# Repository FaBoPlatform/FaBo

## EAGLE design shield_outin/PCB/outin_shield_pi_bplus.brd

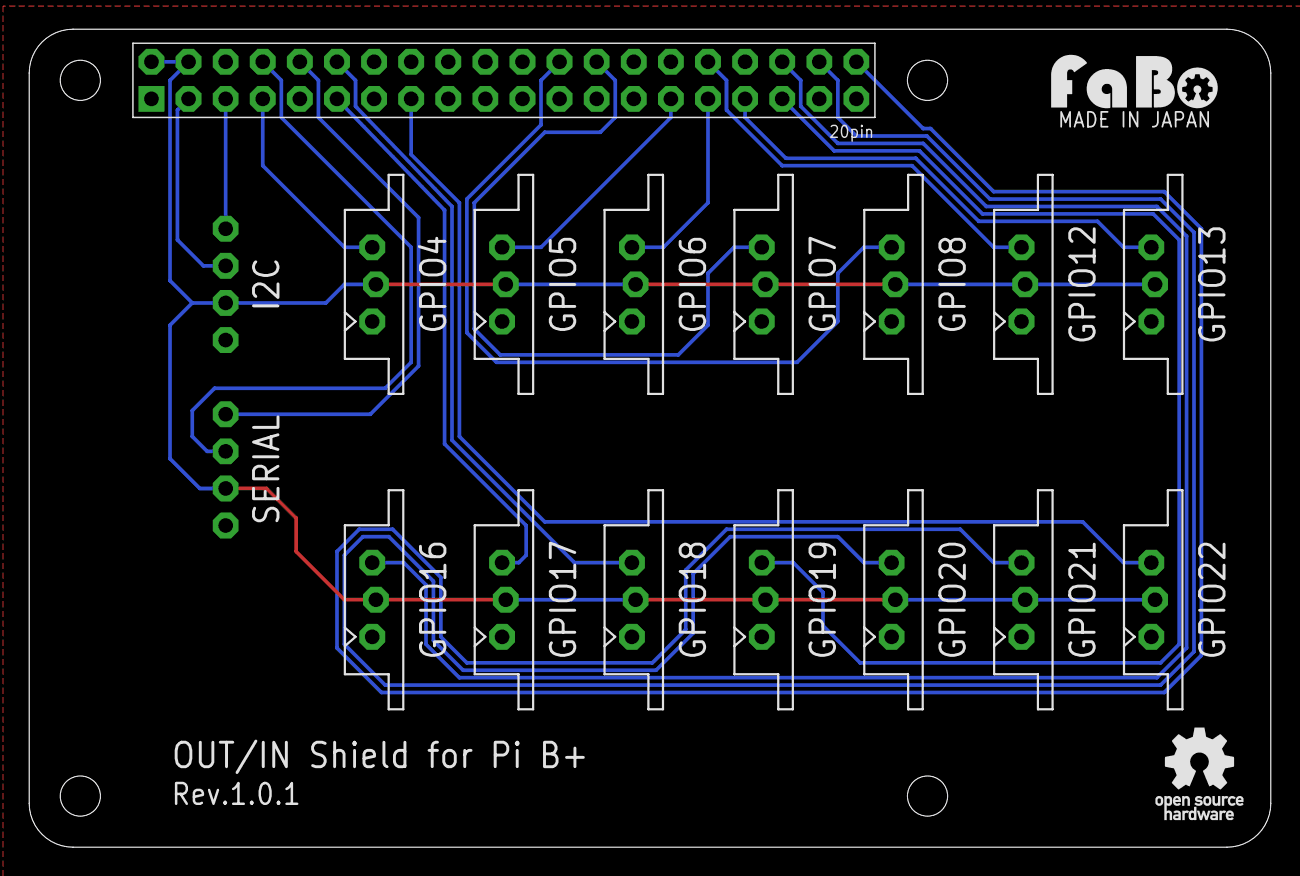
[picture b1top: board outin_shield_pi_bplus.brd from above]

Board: 2 copper layers, 85.0 x 56.0 mm, 19 parts (0 on the bottom side), 20 nets.

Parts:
GPIO4, GPIO5, GPIO6, GPIO7, GPIO8, GPIO12, GPIO13, GPIO16, GPIO17, GPIO18, GPIO19, GPIO20, GPIO21, GPIO22: FABO_BRICK_3PIN_HEADER
I2C: FABO_BRICK_I2C_CONNECTOR
SERIAL: FABO_BRICK_SERIAL_CONNECTOR
U1: RASPBERRY_PI_B+
U$4: LOGO_OSHW_T_M
U$14: LOGO_FABO_M

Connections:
5V: GPIO4.VCC, GPIO5.VCC, GPIO6.VCC, GPIO7.VCC, GPIO8.VCC, GPIO12.VCC, GPIO13.VCC, GPIO16.VCC, GPIO17.VCC, GPIO18.VCC, GPIO19.VCC, GPIO20.VCC, GPIO21.VCC, GPIO22.VCC, I2C.VCC, SERIAL.VCC, U1.2, U1.4
GND: GPIO4.GND, GPIO5.GND, GPIO6.GND, GPIO7.GND, GPIO8.GND, GPIO12.GND, GPIO13.GND, GPIO16.GND, GPIO17.GND, GPIO18.GND, GPIO19.GND, GPIO20.GND, GPIO21.GND, GPIO22.GND, I2C.GND, SERIAL.GND, U1.6, U1.9, U1.14, U1.20, U1.25, U1.30, U1.34, U1.39
GPIO4: GPIO4.I/O, U1.7
GPIO5: GPIO5.I/O, U1.29
GPIO6: GPIO6.I/O, U1.31
GPIO7: GPIO7.I/O, U1.26
GPIO8: GPIO8.I/O, U1.24
GPIO12: GPIO12.I/O, U1.32
GPIO13: GPIO13.I/O, U1.33
GPIO16: GPIO16.I/O, U1.36
GPIO17: GPIO17.I/O, U1.11
GPIO18: GPIO18.I/O, U1.12
GPIO19: GPIO19.I/O, U1.35
GPIO20: GPIO20.I/O, U1.38
GPIO21: GPIO21.I/O, U1.40
GPIO22: GPIO22.I/O, U1.15
RX: SERIAL.RX, U1.10
SCL: I2C.SCL, U1.5
SDA: I2C.SDA, U1.3
TX: SERIAL.TX, U1.8

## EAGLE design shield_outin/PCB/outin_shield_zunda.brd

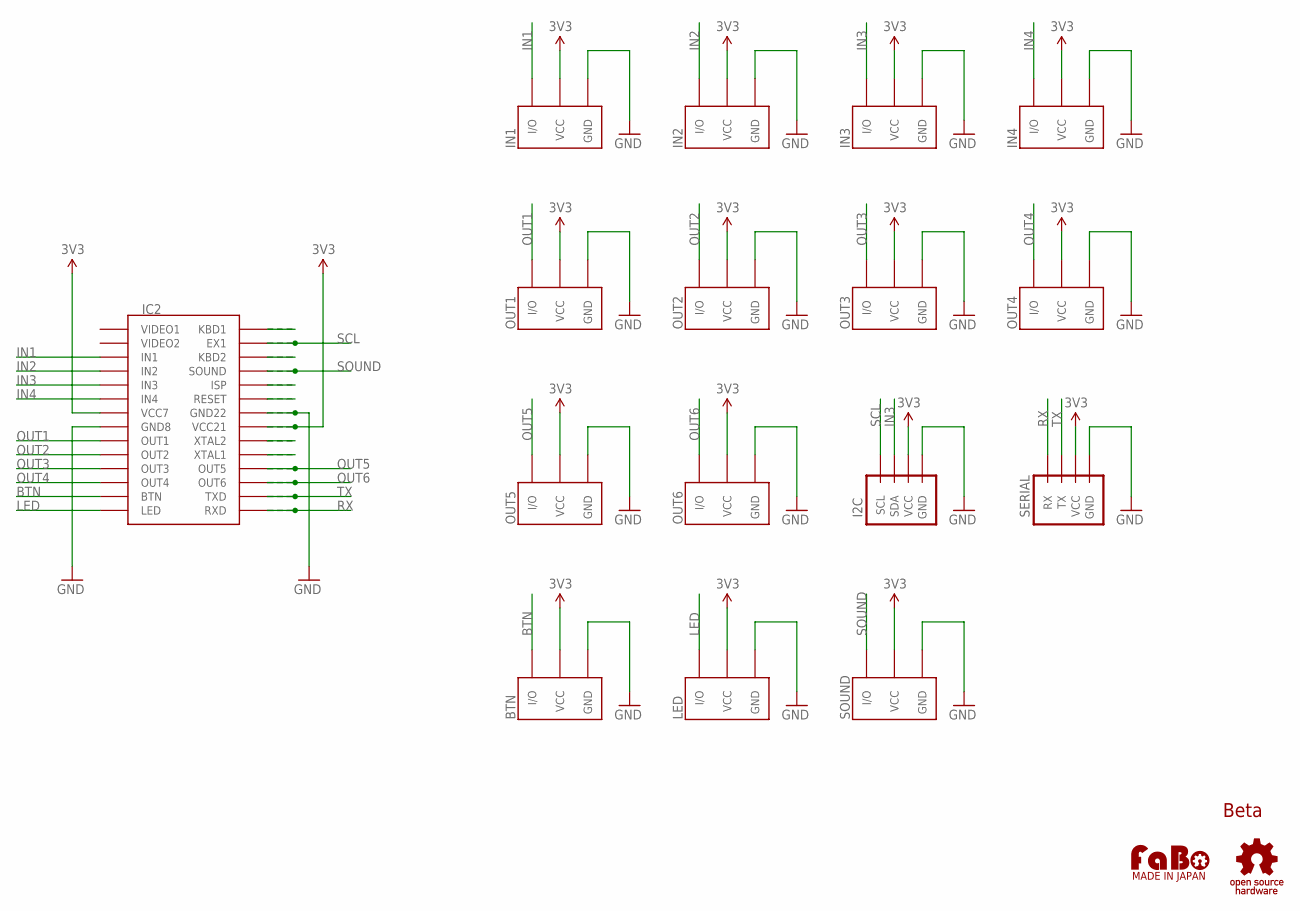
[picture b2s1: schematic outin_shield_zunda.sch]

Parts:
BTN: BRICK_3PIN_CONNECTOR
I2C: BRICK_I2C_CONNECTOR
IN1, IN2, IN3, IN4: BRICK_3PIN_CONNECTOR
LED: BRICK_3PIN_CONNECTOR
OUT1, OUT2, OUT3, OUT4, OUT5, OUT6: BRICK_3PIN_CONNECTOR
SERIAL: BRICK_SERIAL_CONNECTOR
SOUND: BRICK_3PIN_CONNECTOR
U$1: ICHIGOJAM-HOLE; ICHIGOJAM_HOLE
U$3: LOGO_FABO-M; LOGO_FABO_M
U$4: LOGO_OSHW_T-M; LOGO_OSHW_T_M

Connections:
3V3: BTN.VCC, I2C.VCC, IN1.VCC, IN2.VCC, IN3.VCC, IN4.VCC, LED.VCC, OUT1.VCC, OUT2.VCC, OUT3.VCC, OUT4.VCC, OUT5.VCC, OUT6.VCC, SERIAL.VCC, SOUND.VCC, U$1.VCC7, U$1.VCC21, U$1.VCC21-2
BTN: BTN.IN/OUT (I/O), U$1.BTN
GND: BTN.GND, I2C.GND, IN1.GND, IN2.GND, IN3.GND, IN4.GND, LED.GND, OUT1.GND, OUT2.GND, OUT3.GND, OUT4.GND, OUT5.GND, OUT6.GND, SERIAL.GND, SOUND.GND, U$1.GND8, U$1.GND22, U$1.GND22-2
IN1: IN1.IN/OUT (I/O), U$1.IN1
IN2: IN2.IN/OUT (I/O), U$1.IN2
IN3: I2C.SDA, IN3.IN/OUT (I/O), U$1.IN3
IN4: IN4.IN/OUT (I/O), U$1.IN4
LED: LED.IN/OUT (I/O), U$1.LED
unnamed: U$1.KBD1, U$1.KBD1-2
unnamed: U$1.KBD2, U$1.KBD2-2
unnamed: U$1.ISP, U$1.ISP-2
unnamed: U$1.RESET, U$1.RESET-2
unnamed: U$1.XTAL2, U$1.XTAL2-2
unnamed: U$1.XTAL1, U$1.XTAL1-2
OUT1: OUT1.IN/OUT (I/O), U$1.OUT1
OUT2: OUT2.IN/OUT (I/O), U$1.OUT2
OUT3: OUT3.IN/OUT (I/O), U$1.OUT3
OUT4: OUT4.IN/OUT (I/O), U$1.OUT4
OUT5: OUT5.IN/OUT (I/O), U$1.OUT5, U$1.OUT5-2
OUT6: OUT6.IN/OUT (I/O), U$1.OUT6, U$1.OUT6-2
RX: SERIAL.RX, U$1.RXD, U$1.RXD-2
SCL: I2C.SCL, U$1.EX1, U$1.EX1-2
SOUND: SOUND.IN/OUT (I/O), U$1.SOUND, U$1.SOUND-2
TX: SERIAL.TX, U$1.TXD, U$1.TXD-2

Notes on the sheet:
Beta
MADE IN JAPAN

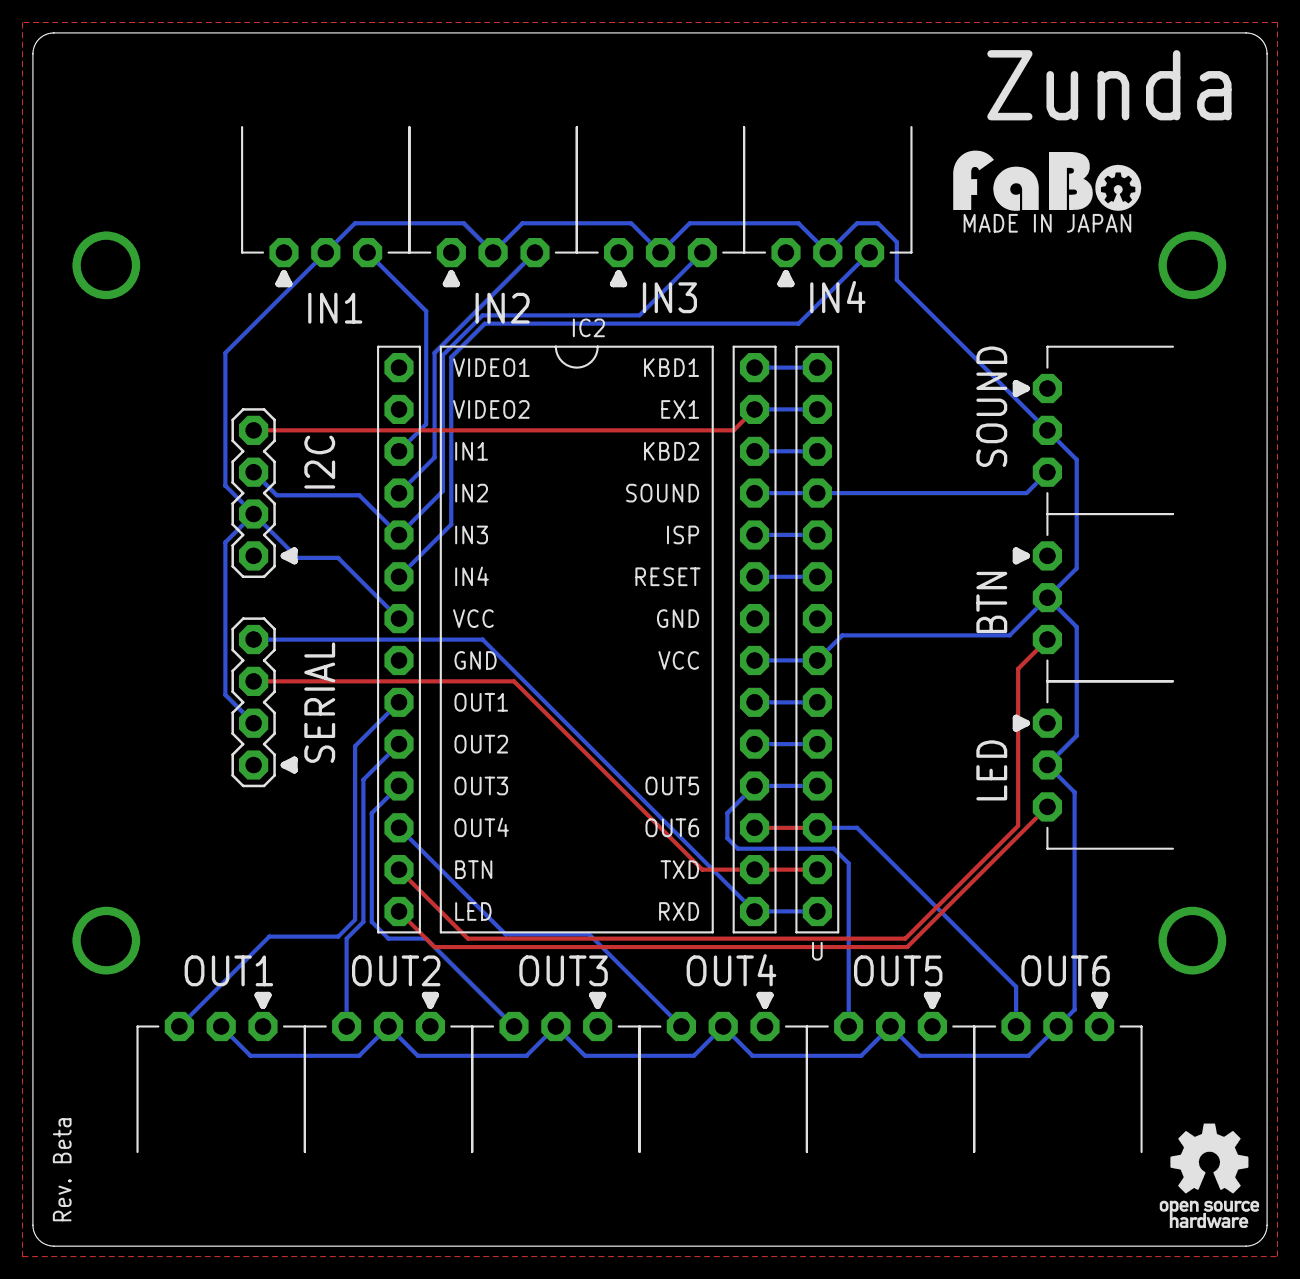
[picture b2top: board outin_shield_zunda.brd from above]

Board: 2 copper layers, 74.9 x 73.7 mm, 18 parts (0 on the bottom side), 24 nets.

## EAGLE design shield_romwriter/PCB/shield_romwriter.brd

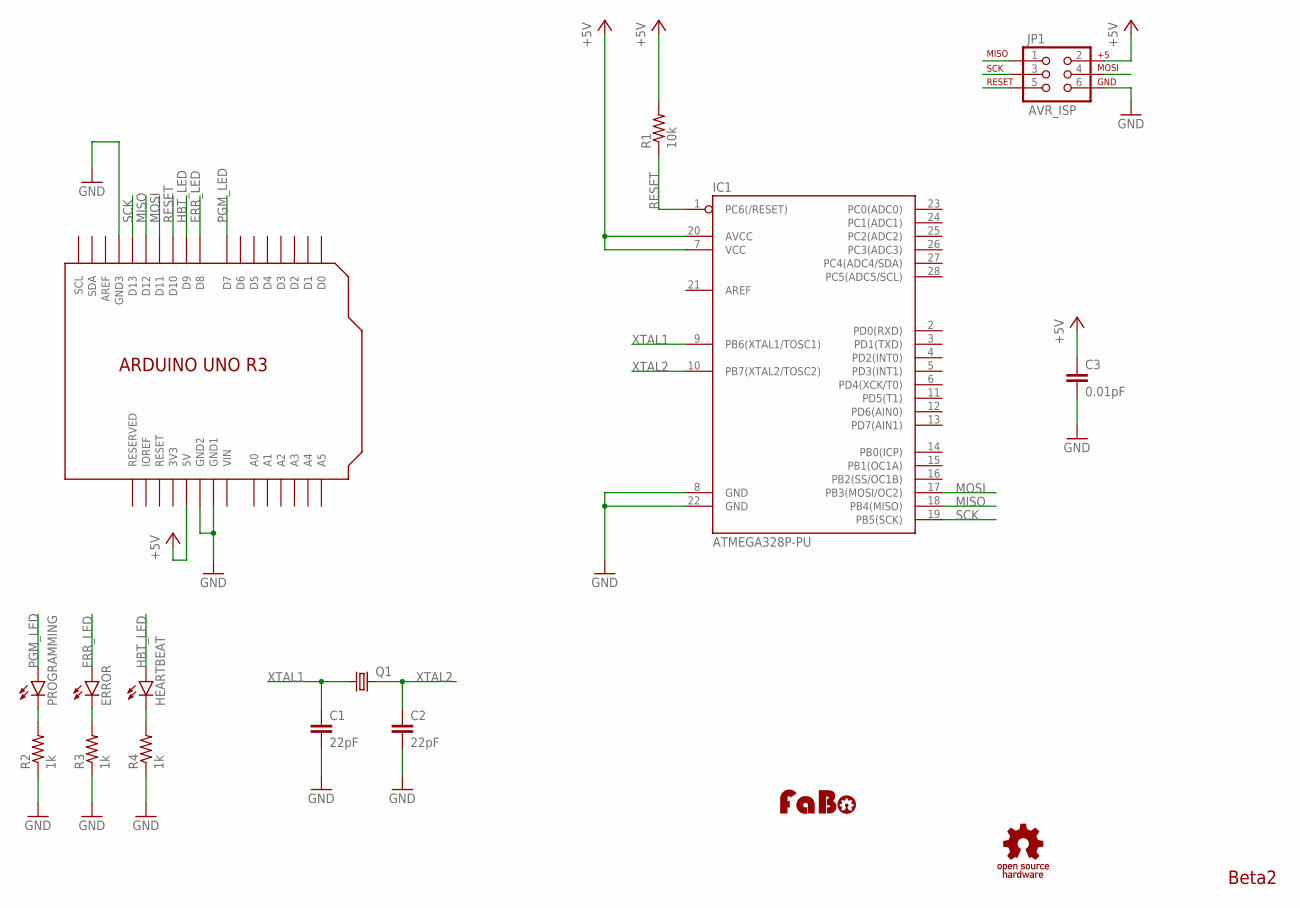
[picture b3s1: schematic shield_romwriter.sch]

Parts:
C1, C2: 22pF; CAP-PTH-SMALL
C3: 0.01pF; CAP-PTH-SMALL
ERROR: LED3MM
HEARTBEAT: LED3MM
IC1: ATMEGA328P-PU; DIL28
JP1: AVR_ISP; 2X3_LOCK
PROGRAMMING: LED3MM
Q1: CRYSTALHC49S; HC49/S
R1: 10k; RES-AXL-REGULAR
R2, R3, R4: 1k; RES-AXL-REGULAR
U2: ARDUINO_UNO_R3_SHIELD-NOLABEL; ARDUINO_UNO_R3_NOLABEL
U$1: LOGO_FABO-M; LOGO_FABO_M
U$3: LOGO_OSHW_T-M; LOGO_OSHW_T_M

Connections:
3V3: U2.3V3
+5V: C3.1, IC1.7 (VCC), IC1.20 (AVCC), JP1.2, R1.P$2 (2), U2.5V
ERR_LED: ERROR.A, U2.D8
GND: C1.2, C2.2, C3.2, IC1.8 (GND), IC1.22 (GND), JP1.6, R2.P$1 (1), R3.P$1 (1), R4.P$1 (1), U2.GND1, U2.GND2, U2.GND3
HBT_LED: HEARTBEAT.A, U2.D9
MISO: IC1.18 (PB4(MISO)), JP1.1, U2.D12
MOSI: IC1.17 (PB3(MOSI/OC2)), JP1.4, U2.D11
unnamed: PROGRAMMING.K (C), R2.P$2 (2)
unnamed: ERROR.K (C), R3.P$2 (2)
unnamed: HEARTBEAT.K (C), R4.P$2 (2)
PGM_LED: PROGRAMMING.A, U2.D7
RESET: IC1.1 (PC6(/RESET)), JP1.5, R1.P$1 (1), U2.D10
SCK: IC1.19 (PB5(SCK)), JP1.3, U2.D13
VIN: U2.VIN
XTAL1: C1.1, IC1.9 (PB6(XTAL1/TOSC1)), Q1.1
XTAL2: C2.1, IC1.10 (PB7(XTAL2/TOSC2)), Q1.2

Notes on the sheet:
Beta2

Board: 2 copper layers, 16 parts (0 on the bottom side), 14 nets, no tracks yet.

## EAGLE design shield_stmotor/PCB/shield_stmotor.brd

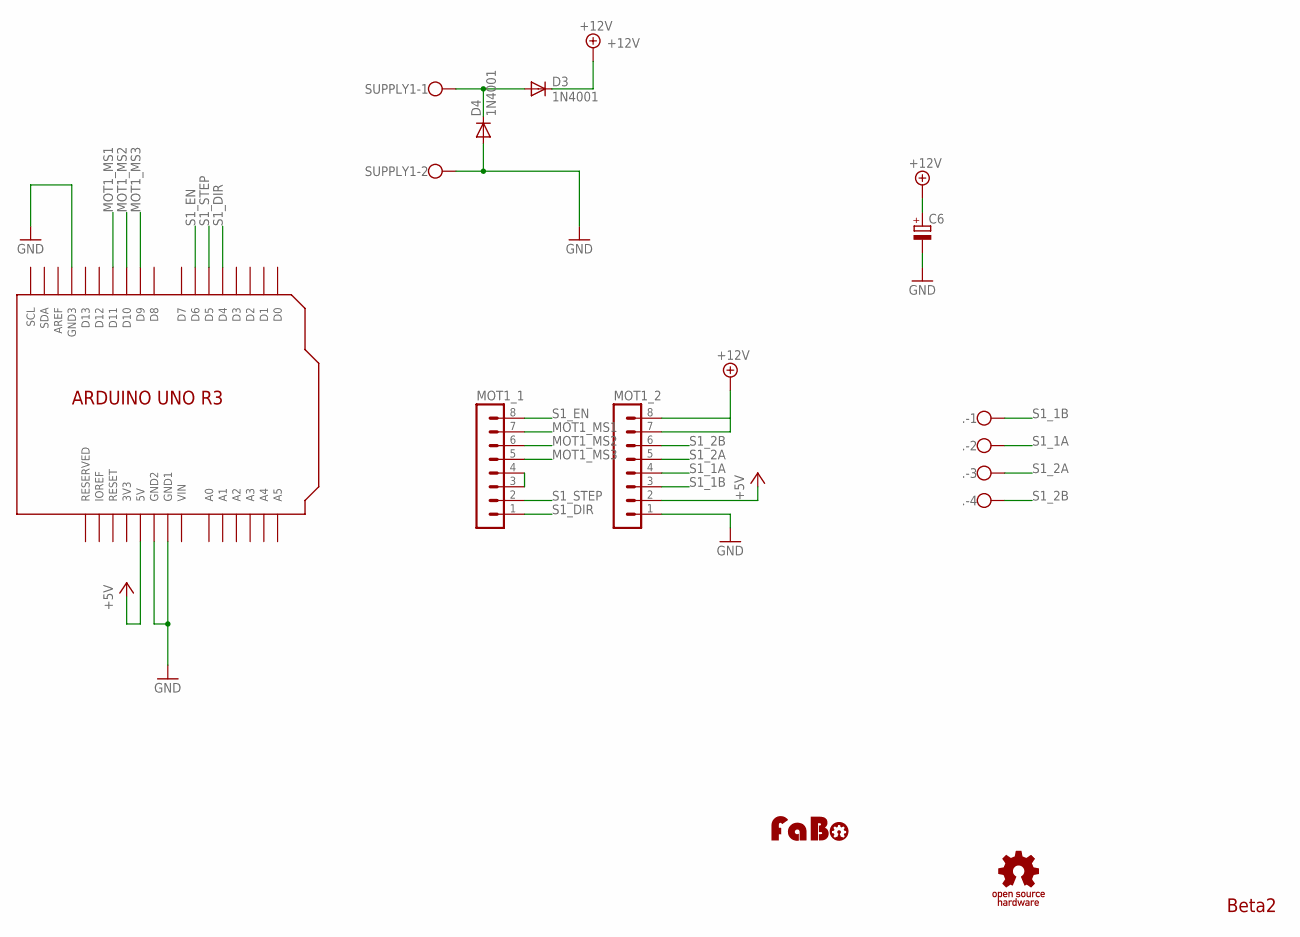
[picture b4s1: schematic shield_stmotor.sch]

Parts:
.: W237-4
C6: CPOL-EU153CLV-0807; 153CLV-0807
D3, D4: 1N4001; DO41-10
MOT1_1, MOT1_2: MA08-1
SUPPLY1: W237-102
U1: ARDUINO_UNO_R3_SHIELD; ARDUINO_UNO_R3
U$1: LOGO_FABO-M; LOGO_FABO_M
U$2: LOGO_OSHW_T-M; LOGO_OSHW_T_M

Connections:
3V3: U1.3V3
+5V: MOT1_2.2, U1.5V
+12V: C6.+, D3.C, MOT1_2.7
GND: C6.-, D4.A, MOT1_2.1, SUPPLY1.2, U1.GND1, U1.GND2, U1.GND3
MOT1_MS1: MOT1_1.7, U1.D11
MOT1_MS2: MOT1_1.6, U1.D10
MOT1_MS3: MOT1_1.5, U1.D9
unnamed: D3.A, D4.C, SUPPLY1.1
S1_1A: ..2, MOT1_2.4
S1_1B: ..1, MOT1_2.3
S1_2A: ..3, MOT1_2.5
S1_2B: ..4, MOT1_2.6
S1_DIR: MOT1_1.1, U1.D4
S1_EN: MOT1_1.8, U1.D6
S1_RST: MOT1_1.3, MOT1_1.4
S1_STEP: MOT1_1.2, U1.D5
VIN: U1.VIN

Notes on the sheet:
Beta2

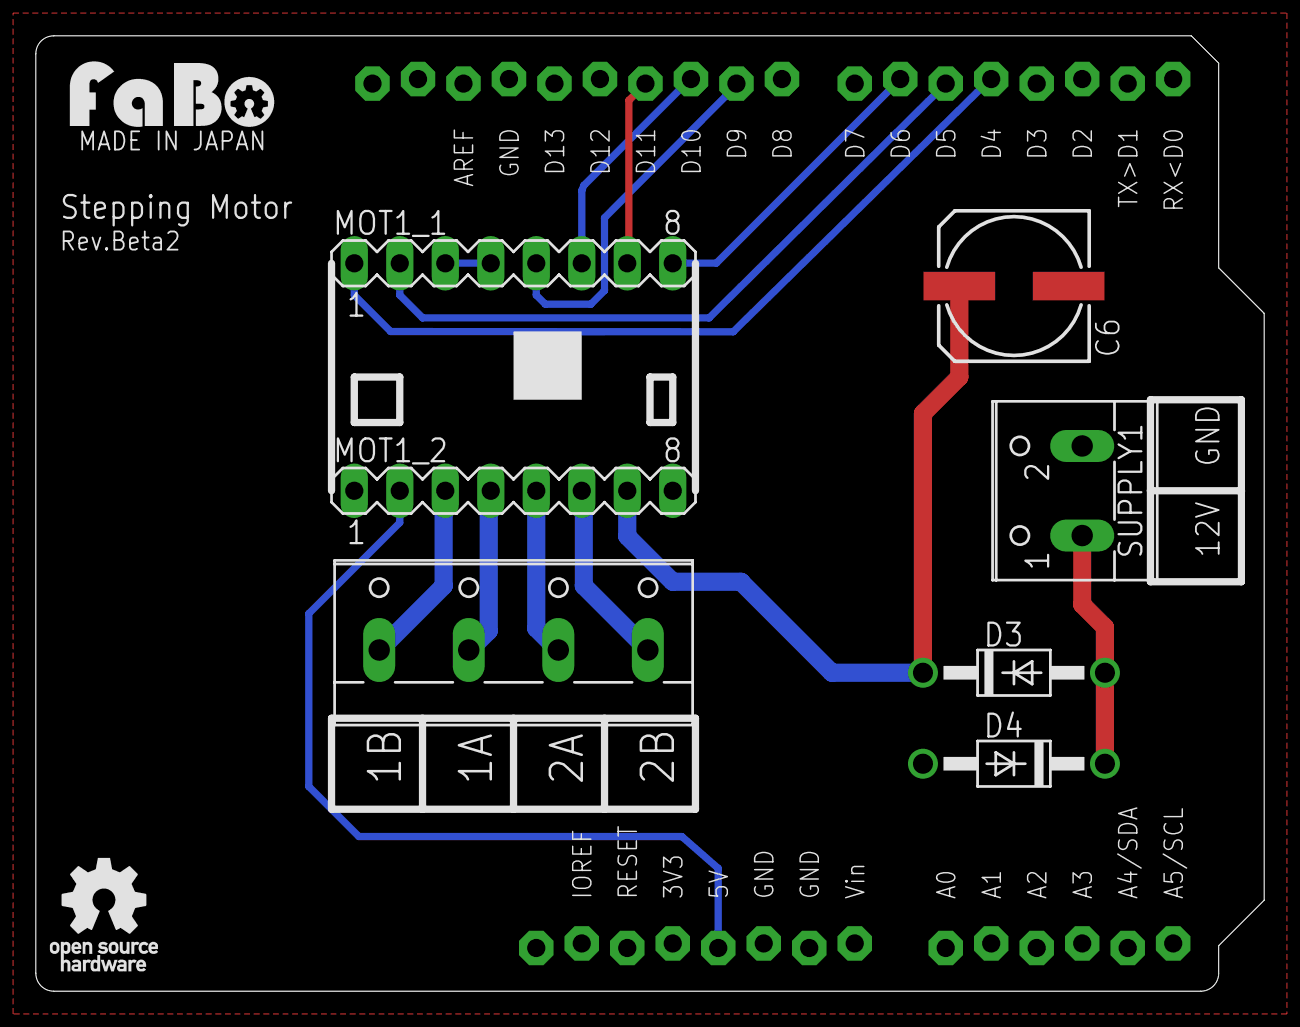
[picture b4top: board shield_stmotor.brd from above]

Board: 2 copper layers, 68.6 x 53.3 mm, 10 parts (0 on the bottom side), 15 nets.

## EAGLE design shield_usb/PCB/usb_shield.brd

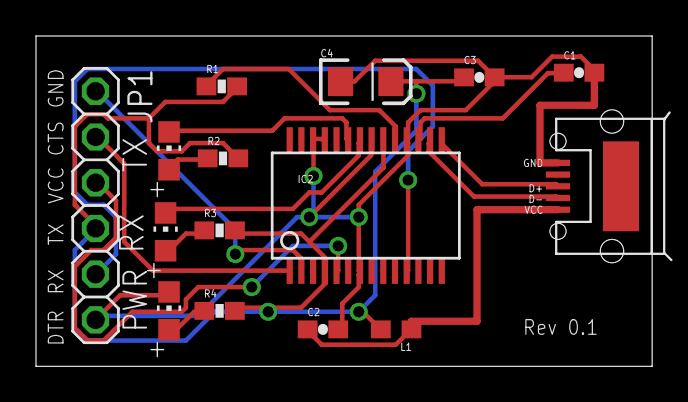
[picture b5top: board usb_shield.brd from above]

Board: 2 copper layers, 34.2 x 18.4 mm, 15 parts (0 on the bottom side), 16 nets.

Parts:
C1, C3: 0.1uf; 0603-CAP
C2: 10nF; 0603-CAP
C4: 10uf; EIA3216
IC2: FT232RLSSOP; SSOP28DB
JP1: 1X06
L1: 0603
PWR: CHIP-LED0805
R1: 47K; 0603-RES
R2, R3, R4: 270; 0603-RES
RX: CHIP-LED0805
TX: CHIP-LED0805
U$1: USB-MICRO-B-FEMALE

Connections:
3.3V: C1.1, IC2.17
CTS: IC2.11, JP1.5
D+: IC2.15, U$1.D+
D-: IC2.16, U$1.D-
DTR: IC2.2, JP1.1
GND: C1.2, C2.2, C3.2, C4.C, IC2.7, IC2.18, IC2.21, IC2.25, IC2.26, JP1.6, PWR.C, U$1.GND
unnamed: C2.1, L1.1, U$1.VCC
unnamed: R2.1, TX.A
unnamed: R3.1, RX.A
unnamed: PWR.A, R4.1
RESET: IC2.19, R1.1
RX: IC2.1, JP1.2
RXLED: IC2.22, RX.C
TX: IC2.5, JP1.3
TXLED: IC2.23, TX.C
VCC: C3.1, C4.A, IC2.4, IC2.20, JP1.4, L1.2, R1.2, R2.2, R3.2, R4.2

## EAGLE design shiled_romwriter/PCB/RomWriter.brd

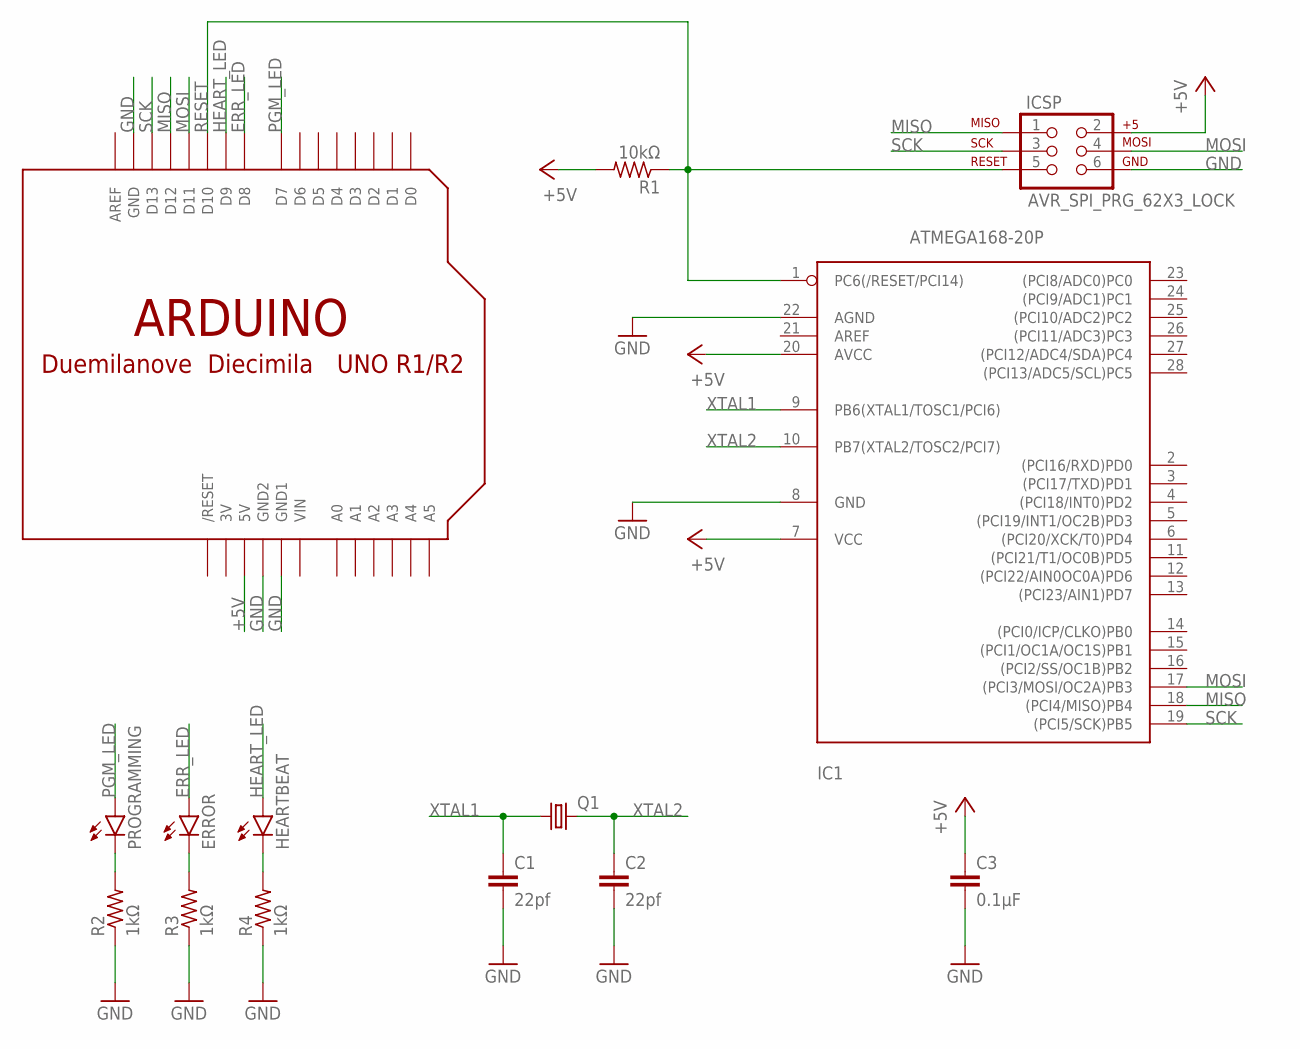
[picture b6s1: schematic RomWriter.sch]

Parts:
C1, C2: 22pf; C2.5-2
C3: 0.1μF; C2.5-2
ERROR: LED3MM
HEARTBEAT: LED3MM
IC1: ATMEGA168-20P; DIL28-3
ICSP: AVR_SPI_PRG_62X3_LOCK; 2X3_LOCK
PROGRAMMING: LED3MM
Q1: CRYSTALHC49S; HC49/S
R1: 10kΩ; 0805-THM
R2, R3, R4: 1kΩ; 0805-THM
U$1: ARDUINO_SHIELD_VER2; ARDUINO_SHIELD

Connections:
3V: U$1.3V
+5V: C3.1, IC1.7 (VCC), IC1.20 (AVCC), ICSP.2, R1.2, U$1.5V
ERR_LED: ERROR.A, U$1.D8
GND: C1.2, C2.2, C3.2, IC1.8 (GND), IC1.22 (AGND), ICSP.6, R2.1, R3.1, R4.1, U$1.GND, U$1.GND1, U$1.GND2
HEART_LED: HEARTBEAT.A, U$1.D9
MISO: IC1.18 ((PCI4/MISO)PB4), ICSP.1, U$1.D12
MOSI: IC1.17 ((PCI3/MOSI/OC2A)PB3), ICSP.4, U$1.D11
unnamed: PROGRAMMING.K (C), R2.2
unnamed: ERROR.K (C), R3.2
unnamed: HEARTBEAT.K (C), R4.2
PGM_LED: PROGRAMMING.A, U$1.D7
RESET: IC1.1 (PC6(/RESET/PCI14)), ICSP.5, R1.1, U$1.D10
SCK: IC1.19 ((PCI5/SCK)PB5), ICSP.3, U$1.D13
VIN: U$1.VIN
XTAL1: C1.1, IC1.9 (PB6(XTAL1/TOSC1/PCI6)), Q1.1
XTAL2: C2.1, IC1.10 (PB7(XTAL2/TOSC2/PCI7)), Q1.2

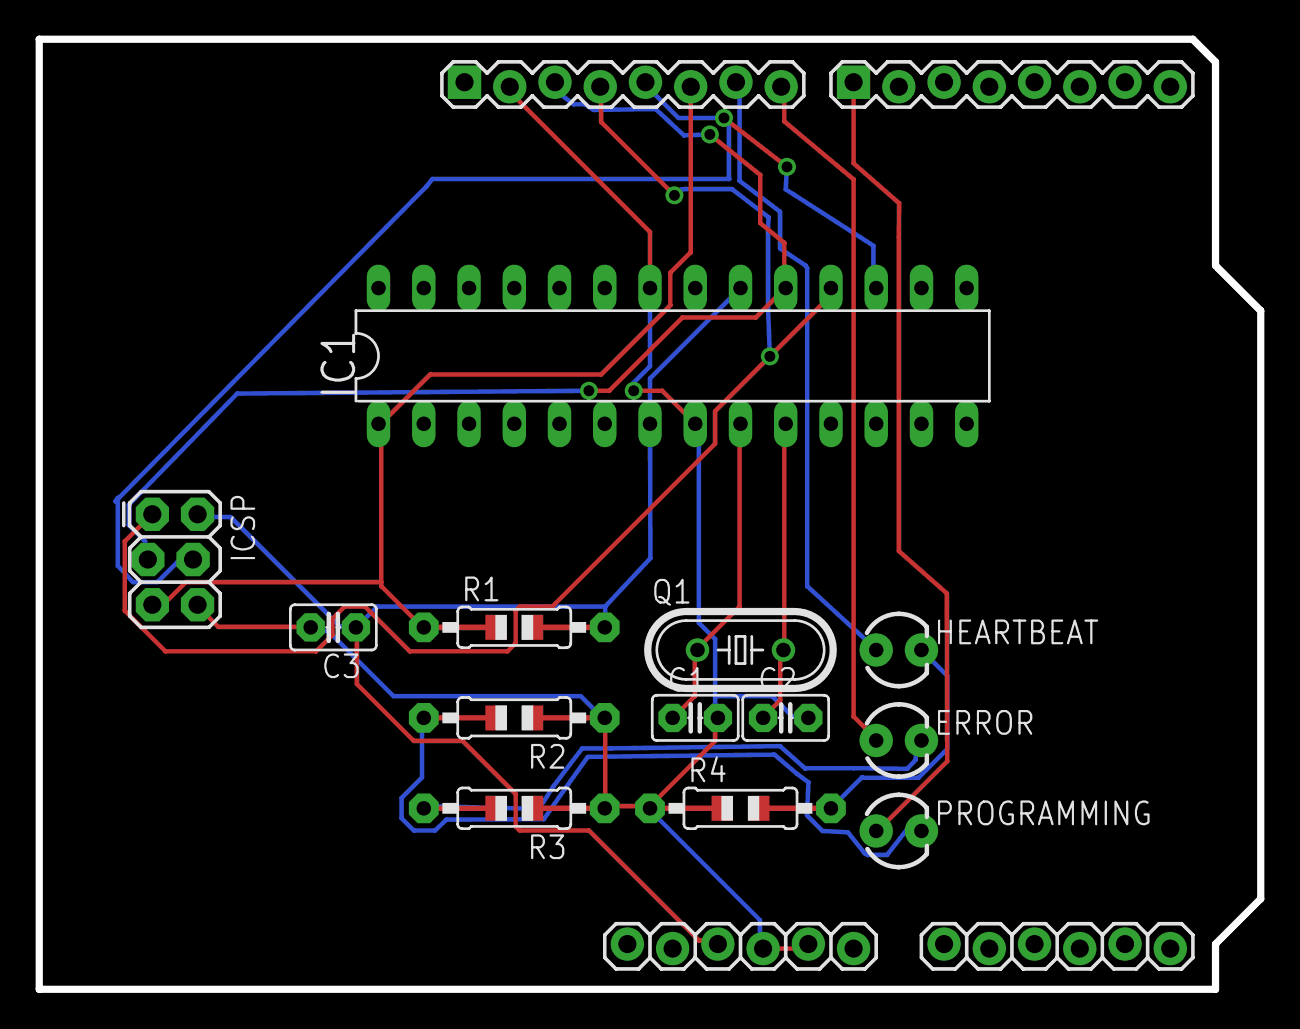
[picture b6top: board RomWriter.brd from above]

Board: 2 copper layers, 68.6 x 53.3 mm, 14 parts (0 on the bottom side), 14 nets.

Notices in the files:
parts and their libraries:
FaBo-etc: Released under the Creative Commons Attribution-ShareAlike 4.0 License
https://creativecommons.org/licenses/by-sa/4.0
GClue: Released under the Creative Commons
SparkFun-LED: Licensing: Creative Commons ShareAlike 4.0 International - https://creativecommons.org/licenses/by-sa/4.0
